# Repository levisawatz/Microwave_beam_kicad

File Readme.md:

# Steerable Microwave Beam Phased Array
Designer: Levi Sawatzky  
Overview Document: https://levisawatz.github.io/assets/microwave_beam/Project_summary.pdf  
Status: In production

## Project Overview 
This project explores the design and construction of a steerable microwave phased array capable of delivering a tightly focused beam of microwave energy toward a target. The system serves as a science demonstration platform that reveals the power and elegance of microwave circuit design, phased arrays, and high-frequency PCB engineering. The core concept is to electronically steer a beam of RF energy without any moving mechanical parts, using phase control across an array of patch antennas. This beam can then be used to transfer wireless power across a distance, light up LEDs, heat up food like a microwave, or boost WIFI 

This PCB was created using Kicad 10

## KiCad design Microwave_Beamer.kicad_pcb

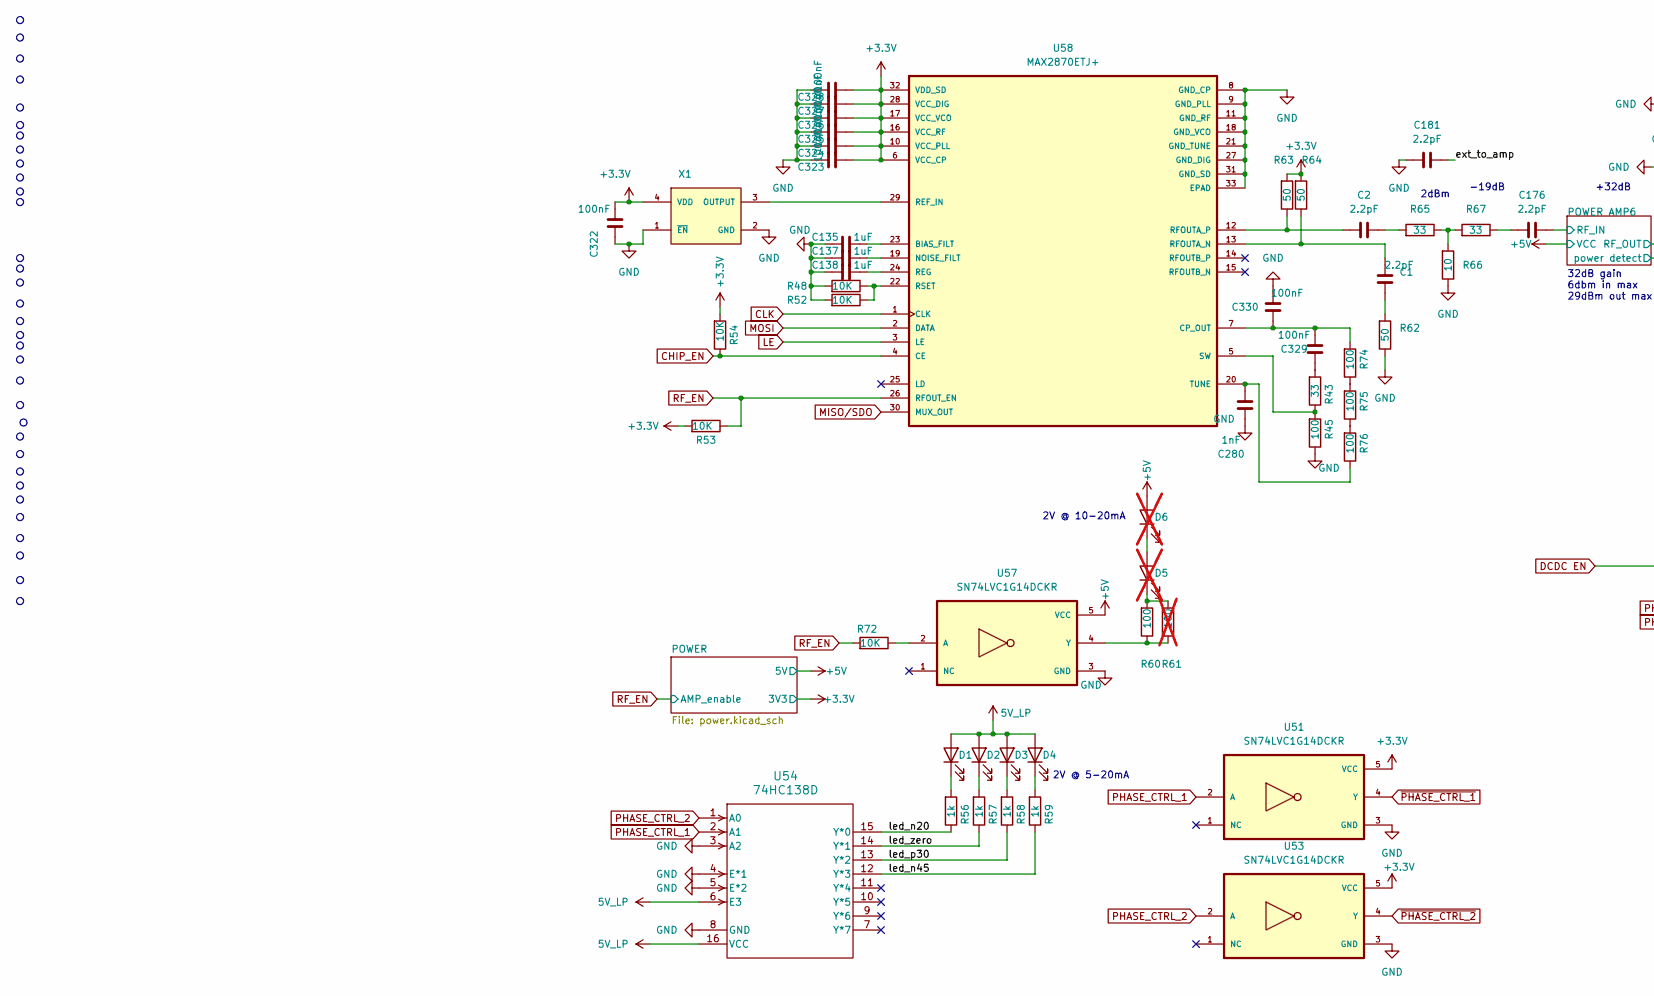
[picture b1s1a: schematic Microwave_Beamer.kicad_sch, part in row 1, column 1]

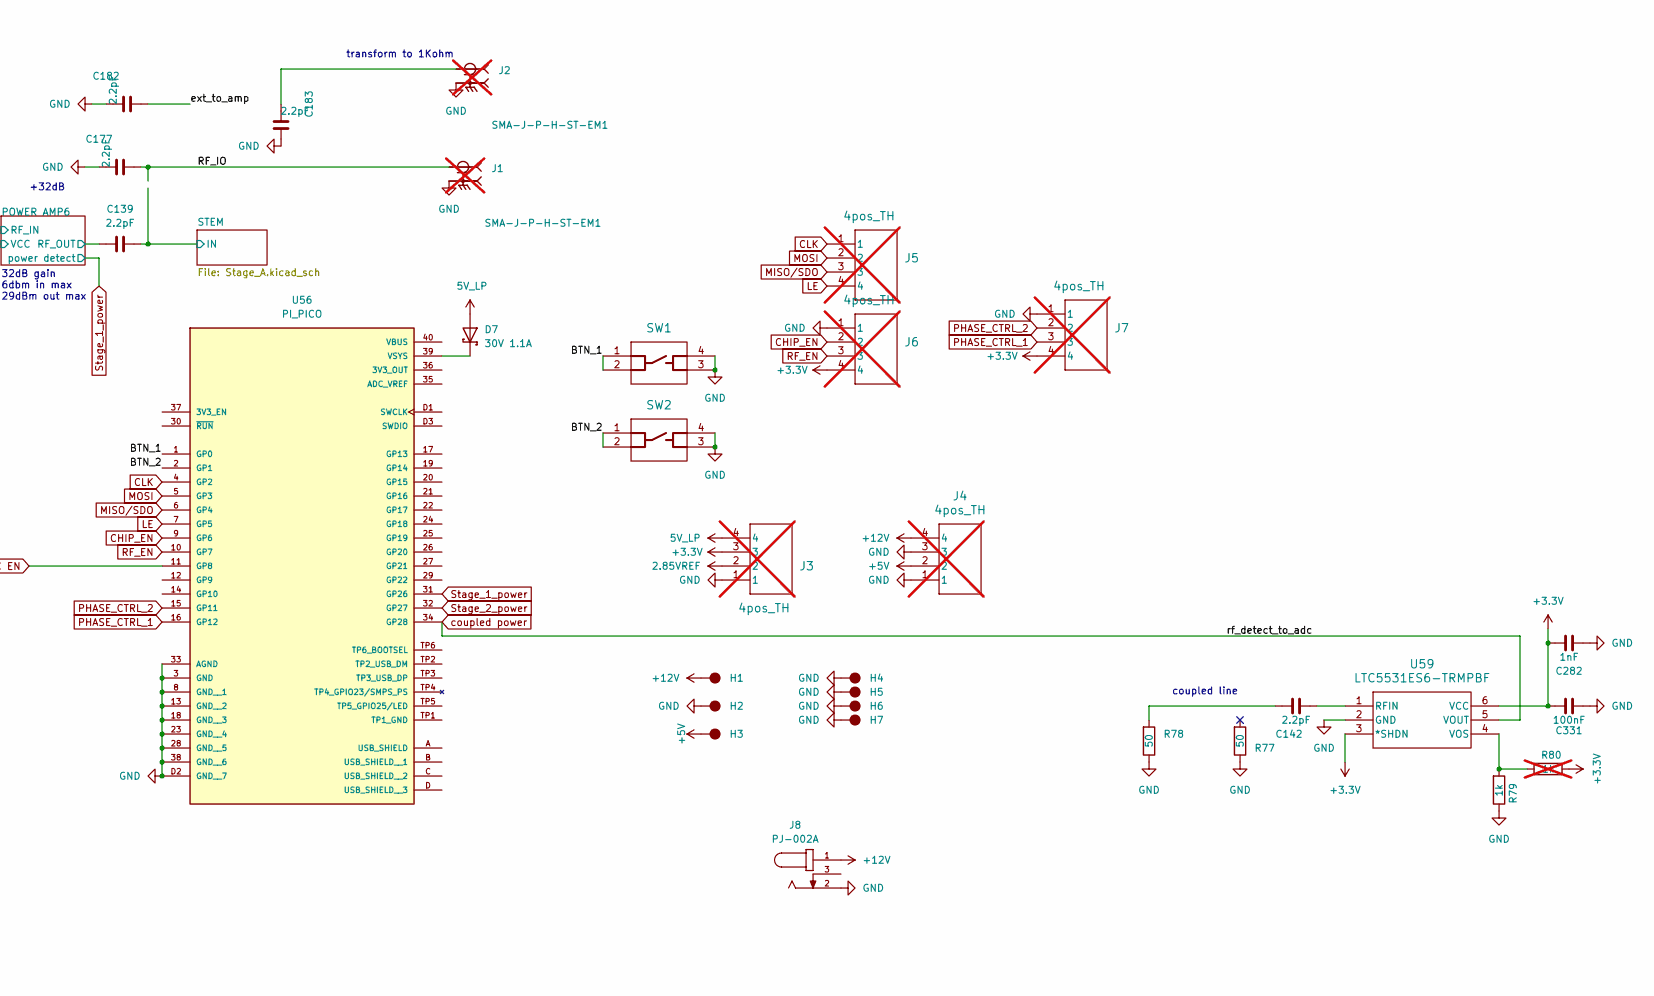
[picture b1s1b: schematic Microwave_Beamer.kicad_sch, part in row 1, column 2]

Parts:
C1, C2, C176: 2.2pF; C_0402_1005Metric; MPN GJM1555C1H2R2WB01D
C135, C137, C138: 1uF; C_0603_1608Metric; MPN GRT188R61H105KE13D
C139, C142, C177, C181, C182, C183: 2.2pF; C_0402_1005Metric_Pad0.74x0.62mm_HandSolder; MPN GJM1555C1H2R2WB01D
C280, C282: 1nF; C_0402_1005Metric; MPN GCM1555C1H102GA16J
C322, C323, C324, C325, C326, C327, C328, C329, C330, C331: 100nF; C_0402_1005Metric; MPN GCM155R71H104KE02J
D1, D2, D3, D4: LTST-C230KGKT; LED_1206_3216Metric; MPN LTST-C230KGKT
D5, D6: LTST-C230KGKT; LED_1206_3216Metric; MPN LTST-C230KRKT; not fitted
D7: 30V 1.1A; CR_03-GS08_VIS; MPN SL03-GS08
H1, H2, H3, H4, H5, H6, H7: Hole; PTH_5mm; MPN DNP
J1, J2: SMA-J-P-H-ST-EM1; SAMTEC_SMA-J-P-H-ST-EM1; PARTREV G; not fitted
J3, J4, J5, J6, J7: 4pos_TH; 4POS-2_54-generic; MPN DNP; not fitted
J8: PJ-002A; CUI_PJ-002A; MPN PJ-002A
R43, R65, R67: 33; R_0402_1005Metric; MPN TNPW040233R0DEED
R45, R60, R74, R75, R76: 100; R_0402_1005Metric; MPN ERA-2AED101X
R48, R52, R53, R54, R72: 10K; R_0603_1608Metric; MPN ERA-3AEB103V
R56, R57, R58, R59, R79: 1k; R_0603_1608Metric; MPN ERA-3AEB102V
R61: 100; R_0402_1005Metric; MPN ERA-2AED101X; not fitted
R62, R63, R64: 50; R_0402_1005Metric; MPN TNPW040249R9BEED
R66: 10; R_0402_1005Metric; MPN TNPW040210R0DEED
R77, R78: 50; R_0402_1005Metric_Pad0.72x0.64mm_HandSolder; MPN TNPW040249R9BEED
R80: 1k; R_0603_1608Metric; MPN ERA-3AEB102V; not fitted
SW1, SW2: PTS526SM15SMTR2 LFS; SON4_PTS526 SM15 SMTR2 LFS_CNK-M; MPN PTS526SM15SMTR2 LFS
U51, U53, U57: SN74LVC1G14DCKR; SOT65P210X110-5N; MPN SN74LVC1G14DCKR
U54: 74HC138D; SOT109-1_NXP; MPN MC74HC138ADR2G
U56: PI_PICO; PI_PICO_SMD; MPN SC0917
U58: MAX2870ETJ+; vco_QFN50P500X500X80-33N; MPN MAX2870ETJ+
U59: LTC5531ES6-TRMPBF; SOT-6_S_LIT-M; MPN LTC5531ES6#TRMPBF
X1: ECS-3225MVQ-1000-CN-TR; OSC_ECS-3225MVQ-1000-CN-TR; MPN ECS-3225MVQ-1000-CN-TR

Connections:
2.85VREF: J3.2; also elsewhere on the board
5V_LP: D1.2 (A), D2.2 (A), D3.2 (A), D4.2 (A), D7.A, J3.4, U54.6 (E3), U54.16 (VCC); also elsewhere on the board
+3.3V: C282.1, C322.2, C323.2, C324.2, C325.2, C326.2, C327.2, C328.2, C331.1, J3.3, J6.4, J7.4, R53.1, R54.1, R63.1, R64.1, R80.2, U51.5 (VCC), U53.5 (VCC), U58.6 (VCC_CP), U58.10 (VCC_PLL), U58.16 (VCC_RF), U58.17 (VCC_VCO), U58.28 (VCC_DIG), U58.32 (VDD_SD), U59.3 (*SHDN), U59.6 (VCC), X1.4 (VDD); also elsewhere on the board
+5V: D6.2 (A), H3.1, J4.2, U57.5 (VCC); also elsewhere on the board
+12V: H1.1, J4.4, J8.1; also elsewhere on the board
/BTN_1: SW1.1, SW1.2, U56.1 (GP0)
/BTN_2: SW2.1, SW2.2, U56.2 (GP1)
/POWER AMP6/RF_IN: C176.2; also elsewhere on the board
/POWER AMP6/RF_OUT: C139.1; also elsewhere on the board
/RF_IO: C177.2, J1.1
/STEM/IN: C139.2; also elsewhere on the board
/ext_to_amp: C181.2, C182.2
/led_n20: R56.2, U54.15 (Y*0)
/led_n45: R59.2, U54.12 (Y*3)
/led_p30: R58.2, U54.13 (Y*2)
/led_zero: R57.2, U54.14 (Y*1)
CHIP_EN: J6.2, R54.2, U56.9 (GP6), U58.4 (CE)
CLK: J5.1, U56.4 (GP2), U58.1 (CLK)
DCDC EN: U56.11 (GP8); also elsewhere on the board
GND: C135.1, C137.1, C138.1, C177.1, C181.1, C182.1, C183.2, C280.2, C282.2, C322.1, C323.1, C324.1, C325.1, C326.1, C327.1, C328.1, C330.1, C331.2, H2.1, H4.1, H5.1, H6.1, H7.1, J1.2_1, J1.2_2, J1.3_1, J1.3_2, J2.2_1, J2.2_2, J2.3_1, J2.3_2, J3.1, J4.1, J4.3, J6.1, J7.1, J8.2, R45.2, R48.1, R52.1, R62.2, R66.2, R77.2, R78.2, R79.2, SW1.3, SW1.4, SW2.3, SW2.4, U51.3 (GND), U53.3 (GND), U54.3 (A2), U54.4 (E*1), U54.5 (E*2), U54.8 (GND), U56.3 (GND), U56.8 (GND__1), U56.13 (GND__2), U56.18 (GND__3), U56.23 (GND__4), U56.28 (GND__5), U56.33 (AGND), U56.38 (GND__6), U56.D2 (GND__7), U57.3 (GND), U58.8 (GND_CP), U58.9 (GND_PLL), U58.11 (GND_RF), U58.18 (GND_VCO), U58.21 (GND_TUNE), U58.27 (GND_DIG), U58.31 (GND_SD), U58.33 (EPAD), U59.2 (GND), X1.1 (~EN), X1.2 (GND); also elsewhere on the board
LE: J5.4, U56.7 (GP5), U58.3 (LE)
MISO/SDO: J5.3, U56.6 (GP4), U58.30 (MUX_OUT)
MOSI: J5.2, U56.5 (GP3), U58.2 (DATA)
unnamed: C1.2, R62.1
unnamed: C2.2, R65.1
unnamed: C142.1, R78.1
unnamed: C176.1, R67.2
unnamed: C183.1, J2.1
unnamed: C329.2, R43.1
unnamed: D1.1 (K), R56.1
unnamed: D2.1 (K), R57.1
unnamed: D3.1 (K), R58.1
unnamed: D4.1 (K), R59.1
unnamed: D5.2 (A), D6.1 (K)
unnamed: D5.1 (K), R60.1, R61.1
unnamed: R65.2, R66.1, R67.1
unnamed: R74.2, R75.1
unnamed: R75.2, R76.1
unnamed: D7.K, U56.39 (VSYS)
unnamed: R72.2, U57.2 (A)
unnamed: R60.2, R61.2, U57.4 (Y)
unnamed: C135.2, U58.23 (BIAS_FILT)
unnamed: C329.1, C330.2, R74.1, U58.7 (CP_OUT)
unnamed: C137.2, U58.19 (NOISE_FILT)
unnamed: U58.29 (REF_IN), X1.3 (OUTPUT)
unnamed: C138.2, U58.24 (REG)
unnamed: C1.1, R64.2, U58.13 (RFOUTA_N)
unnamed: C2.1, R63.2, U58.12 (RFOUTA_P)
unnamed: R48.2, R52.2, U58.22 (RSET)
unnamed: R43.2, R45.1, U58.5 (SW)
unnamed: C280.1, R76.2, U58.20 (TUNE)
unnamed: C142.2, U59.1 (RFIN)
unnamed: R79.1, R80.1, U59.4 (VOS)
PHASE_CTRL_1: J7.3, U51.2 (A), U54.2 (A1), U56.16 (GP12); also elsewhere on the board
PHASE_CTRL_2: J7.2, U53.2 (A), U54.1 (A0), U56.15 (GP11); also elsewhere on the board
RF_EN: J6.3, R53.2, R72.1, U56.10 (GP7), U58.26 (RFOUT_EN); also elsewhere on the board
Stage_1_power: U56.31 (GP26); also elsewhere on the board
Stage_2_power: U56.32 (GP27); also elsewhere on the board
coupled power: U56.34 (GP28), U59.5 (VOUT)
~PHASE_CTRL_1: U51.4 (Y); also elsewhere on the board
~PHASE_CTRL_2: U53.4 (Y); also elsewhere on the board

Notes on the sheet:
coupled line
2V @ 10-20mA
32dB gain 6dbm in max 29dBm out max
2dBm
-19dB
transform to 1Kohm
2V @ 5-20mA
+32dB

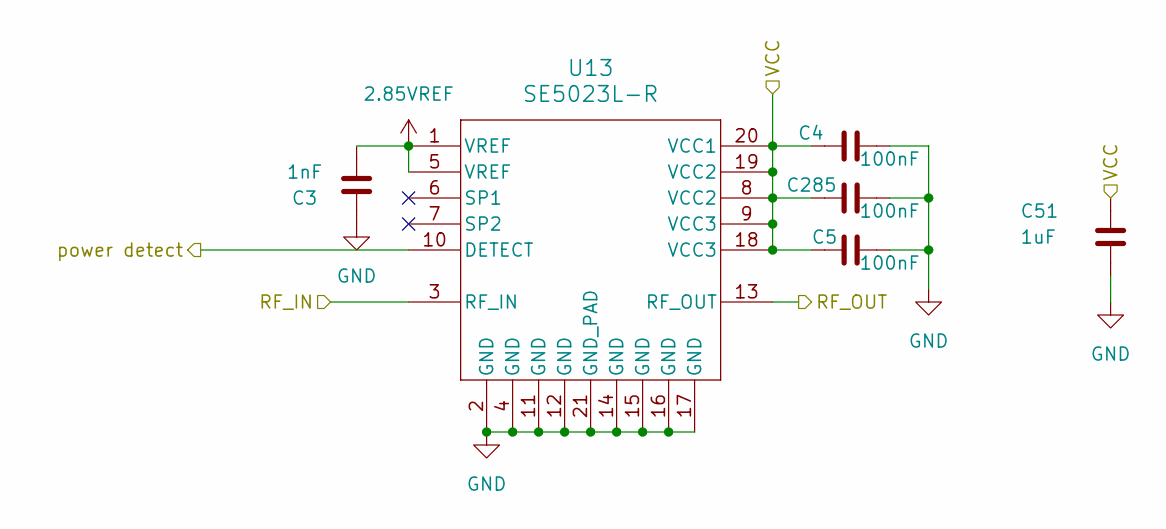
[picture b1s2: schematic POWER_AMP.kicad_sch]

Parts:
C3: 1nF; C_0402_1005Metric; MPN GCM1555C1H102GA16J
C4, C5, C285: 100nF; C_0402_1005Metric; MPN GCM155R71H104KE02J
C51: 1uF; C_0603_1608Metric; MPN GRT188R61H105KE13D
U13: SE5023L-R; QFN20_4X4_STM; MPN SE5023L-R

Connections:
2.85VREF: C3.1, U13.1 (VREF), U13.5 (VREF); also elsewhere on the board
+5V: C4.1, C5.1, C51.1, C285.1, U13.8 (VCC2), U13.9 (VCC3), U13.18 (VCC3), U13.19 (VCC2), U13.20 (VCC1); also elsewhere on the board
/STEM/FAN_A/Antenna_1: U13.13 (RF_OUT)
/STEM/FAN_A/FANFAN A/OUT1: U13.3 (RF_IN); also elsewhere on the board
/STEM/FAN_A/POWER AMP1/power detect: U13.10 (DETECT)
GND: C3.2, C4.2, C5.2, C51.2, C285.2, U13.2 (GND), U13.4 (GND), U13.11 (GND), U13.12 (GND), U13.14 (GND), U13.15 (GND), U13.16 (GND), U13.17 (GND), U13.21 (GND_PAD); also elsewhere on the board

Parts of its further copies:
C6, C7, C8, C9, C25, C26, C27, C28, C29, C30, C39, C40, C41, C42, C43, C44, C46, C47, C48, C49, C50, C61, C75, C89, C103, C117, C131, C145, C159, C173, C187, C201, C215, C229, C243, C257, C286, C287, C288, C289, C290, C291, C292, C293, C294, C295, C296, C297, C298, C299, C300, C301, C302, C303: 100nF; C_0402_1005Metric; MPN GCM155R71H104KE02J
C24, C38, C45, C59, C73, C87, C101, C115, C129, C143, C157, C171, C185, C199, C213, C227, C241, C255: 1nF; C_0402_1005Metric; MPN GCM1555C1H102GA16J
C60, C62, C63, C64, C65, C74, C76, C77, C78, C79, C88, C90, C91, C92, C93, C102, C104, C105: 1uF; C_0603_1608Metric; MPN GRT188R61H105KE13D
U16, U18, U19, U21, U23, U25, U27, U29, U31, U33, U35, U37, U39, U41, U43, U45, U47, U49: SE5023L-R; QFN20_4X4_STM; MPN SE5023L-R

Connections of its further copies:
2.85VREF: C24.1, C38.1, C45.1, C59.1, C73.1, C87.1, C101.1, C115.1, C129.1, C143.1, C157.1, C171.1, C185.1, C199.1, C213.1, C227.1, C241.1, C255.1, U16.1 (VREF), U16.5 (VREF), U18.1 (VREF), U18.5 (VREF), U19.1 (VREF), U19.5 (VREF), U21.1 (VREF), U21.5 (VREF), U23.1 (VREF), U23.5 (VREF), U25.1 (VREF), U25.5 (VREF), U27.1 (VREF), U27.5 (VREF), U29.1 (VREF), U29.5 (VREF), U31.1 (VREF), U31.5 (VREF), U33.1 (VREF), U33.5 (VREF), U35.1 (VREF), U35.5 (VREF), U37.1 (VREF), U37.5 (VREF), U39.1 (VREF), U39.5 (VREF), U41.1 (VREF), U41.5 (VREF), U43.1 (VREF), U43.5 (VREF), U45.1 (VREF), U45.5 (VREF), U47.1 (VREF), U47.5 (VREF), U49.1 (VREF), U49.5 (VREF); also elsewhere on the board
+5V: C6.1, C7.1, C8.1, C9.1, C25.1, C26.1, C27.1, C28.1, C29.1, C30.1, C39.1, C40.1, C41.1, C42.1, C43.1, C44.1, C46.1, C47.1, C48.1, C49.1, C50.1, C60.1, C61.1, C62.1, C63.1, C64.1, C65.1, C74.1, C75.1, C76.1, C77.1, C78.1, C79.1, C88.1, C89.1, C90.1, C91.1, C92.1, C93.1, C102.1, C103.1, C104.1, C105.1, C117.1, C131.1, C145.1, C159.1, C173.1, C187.1, C201.1, C215.1, C229.1, C243.1, C257.1, C286.1, C287.1, C288.1, C289.1, C290.1, C291.1, C292.1, C293.1, C294.1, C295.1, C296.1, C297.1, C298.1, C299.1, C300.1, C301.1, C302.1, C303.1, U16.8 (VCC2), U16.9 (VCC3), U16.18 (VCC3), U16.19 (VCC2), U16.20 (VCC1), U18.8 (VCC2), U18.9 (VCC3), U18.18 (VCC3), U18.19 (VCC2), U18.20 (VCC1), U19.8 (VCC2), U19.9 (VCC3), U19.18 (VCC3), U19.19 (VCC2), U19.20 (VCC1), U21.8 (VCC2), U21.9 (VCC3), U21.18 (VCC3), U21.19 (VCC2), U21.20 (VCC1), U23.8 (VCC2), U23.9 (VCC3), U23.18 (VCC3), U23.19 (VCC2), U23.20 (VCC1), U25.8 (VCC2), U25.9 (VCC3), U25.18 (VCC3), U25.19 (VCC2), U25.20 (VCC1), U27.8 (VCC2), U27.9 (VCC3), U27.18 (VCC3), U27.19 (VCC2), U27.20 (VCC1), U29.8 (VCC2), U29.9 (VCC3), U29.18 (VCC3), U29.19 (VCC2), U29.20 (VCC1), U31.8 (VCC2), U31.9 (VCC3), U31.18 (VCC3), U31.19 (VCC2), U31.20 (VCC1), U33.8 (VCC2), U33.9 (VCC3), U33.18 (VCC3), U33.19 (VCC2), U33.20 (VCC1), U35.8 (VCC2), U35.9 (VCC3), U35.18 (VCC3), U35.19 (VCC2), U35.20 (VCC1), U37.8 (VCC2), U37.9 (VCC3), U37.18 (VCC3), U37.19 (VCC2), U37.20 (VCC1), U39.8 (VCC2), U39.9 (VCC3), U39.18 (VCC3), U39.19 (VCC2), U39.20 (VCC1), U41.8 (VCC2), U41.9 (VCC3), U41.18 (VCC3), U41.19 (VCC2), U41.20 (VCC1), U43.8 (VCC2), U43.9 (VCC3), U43.18 (VCC3), U43.19 (VCC2), U43.20 (VCC1), U45.8 (VCC2), U45.9 (VCC3), U45.18 (VCC3), U45.19 (VCC2), U45.20 (VCC1), U47.8 (VCC2), U47.9 (VCC3), U47.18 (VCC3), U47.19 (VCC2), U47.20 (VCC1), U49.8 (VCC2), U49.9 (VCC3), U49.18 (VCC3), U49.19 (VCC2), U49.20 (VCC1); also elsewhere on the board
/POWER AMP6/RF_IN: U49.3 (RF_IN); also elsewhere on the board
/POWER AMP6/RF_OUT: U49.13 (RF_OUT); also elsewhere on the board
/STEM/FAN_A/Antenna_3: U16.13 (RF_OUT)
/STEM/FAN_A/Antenna_5: U18.13 (RF_OUT)
/STEM/FAN_A/FANFAN A/OUT3: U16.3 (RF_IN); also elsewhere on the board
/STEM/FAN_A/FANFAN A/OUT5: U18.3 (RF_IN); also elsewhere on the board
/STEM/FAN_A/POWER AMP3/power detect: U16.10 (DETECT)
/STEM/FAN_A/power_det: U18.10 (DETECT)
/STEM/FAN_B/Antenna_1: U19.13 (RF_OUT)
/STEM/FAN_B/Antenna_3: U21.13 (RF_OUT)
/STEM/FAN_B/Antenna_5: U23.13 (RF_OUT)
/STEM/FAN_B/FANFAN A/OUT1: U19.3 (RF_IN); also elsewhere on the board
/STEM/FAN_B/FANFAN A/OUT3: U21.3 (RF_IN); also elsewhere on the board
/STEM/FAN_B/FANFAN A/OUT5: U23.3 (RF_IN); also elsewhere on the board
/STEM/FAN_B/POWER AMP1/power detect: U19.10 (DETECT)
/STEM/FAN_B/POWER AMP3/power detect: U21.10 (DETECT)
/STEM/FAN_C/Antenna_1: U25.13 (RF_OUT)
/STEM/FAN_C/Antenna_3: U27.13 (RF_OUT)
/STEM/FAN_C/Antenna_5: U29.13 (RF_OUT)
/STEM/FAN_C/FANFAN A/OUT1: U25.3 (RF_IN); also elsewhere on the board
/STEM/FAN_C/FANFAN A/OUT3: U27.3 (RF_IN); also elsewhere on the board
/STEM/FAN_C/FANFAN A/OUT5: U29.3 (RF_IN); also elsewhere on the board
/STEM/FAN_C/POWER AMP1/power detect: U25.10 (DETECT)
/STEM/FAN_C/POWER AMP3/power detect: U27.10 (DETECT)
/STEM/FAN_C/power_det: U29.10 (DETECT)
/STEM/FAN_D/Antenna_1: U31.13 (RF_OUT)
/STEM/FAN_D/Antenna_3: U33.13 (RF_OUT)
/STEM/FAN_D/Antenna_5: U35.13 (RF_OUT)
/STEM/FAN_D/FANFAN A/OUT1: U31.3 (RF_IN); also elsewhere on the board
/STEM/FAN_D/FANFAN A/OUT3: U33.3 (RF_IN); also elsewhere on the board
/STEM/FAN_D/FANFAN A/OUT5: U35.3 (RF_IN); also elsewhere on the board
/STEM/FAN_D/POWER AMP1/power detect: U31.10 (DETECT)
/STEM/FAN_D/POWER AMP3/power detect: U33.10 (DETECT)
/STEM/FAN_D/power_det: U35.10 (DETECT)
/STEM/FAN_E/Antenna_1: U37.13 (RF_OUT)
/STEM/FAN_E/Antenna_3: U39.13 (RF_OUT)
/STEM/FAN_E/Antenna_5: U41.13 (RF_OUT)
/STEM/FAN_E/FANFAN A/OUT1: U37.3 (RF_IN); also elsewhere on the board
/STEM/FAN_E/FANFAN A/OUT3: U39.3 (RF_IN); also elsewhere on the board
/STEM/FAN_E/FANFAN A/OUT5: U41.3 (RF_IN); also elsewhere on the board
/STEM/FAN_E/POWER AMP1/power detect: U37.10 (DETECT)
/STEM/FAN_E/POWER AMP3/power detect: U39.10 (DETECT)
/STEM/FAN_E/power_det: U41.10 (DETECT)
/STEM/FAN_F/Antenna_1: U43.13 (RF_OUT)
/STEM/FAN_F/Antenna_3: U45.13 (RF_OUT)
/STEM/FAN_F/Antenna_5: U47.13 (RF_OUT)
/STEM/FAN_F/FANFAN A/OUT1: U43.3 (RF_IN); also elsewhere on the board
/STEM/FAN_F/FANFAN A/OUT3: U45.3 (RF_IN); also elsewhere on the board
/STEM/FAN_F/FANFAN A/OUT5: U47.3 (RF_IN); also elsewhere on the board
/STEM/FAN_F/POWER AMP1/power detect: U43.10 (DETECT)
/STEM/FAN_F/POWER AMP3/power detect: U45.10 (DETECT)
/STEM/FAN_F/power_det: U47.10 (DETECT)
GND: C6.2, C7.2, C8.2, C9.2, C24.2, C25.2, C26.2, C27.2, C28.2, C29.2, C30.2, C38.2, C39.2, C40.2, C41.2, C42.2, C43.2, C44.2, C45.2, C46.2, C47.2, C48.2, C49.2, C50.2, C59.2, C60.2, C61.2, C62.2, C63.2, C64.2, C65.2, C73.2, C74.2, C75.2, C76.2, C77.2, C78.2, C79.2, C87.2, C88.2, C89.2, C90.2, C91.2, C92.2, C93.2, C101.2, C102.2, C103.2, C104.2, C105.2, C115.2, C117.2, C129.2, C131.2, C143.2, C145.2, C157.2, C159.2, C171.2, C173.2, C185.2, C187.2, C199.2, C201.2, C213.2, C215.2, C227.2, C229.2, C241.2, C243.2, C255.2, C257.2, C286.2, C287.2, C288.2, C289.2, C290.2, C291.2, C292.2, C293.2, C294.2, C295.2, C296.2, C297.2, C298.2, C299.2, C300.2, C301.2, C302.2, C303.2, U16.2 (GND), U16.4 (GND), U16.11 (GND), U16.12 (GND), U16.14 (GND), U16.15 (GND), U16.16 (GND), U16.17 (GND), U16.21 (GND_PAD), U18.2 (GND), U18.4 (GND), U18.11 (GND), U18.12 (GND), U18.14 (GND), U18.15 (GND), U18.16 (GND), U18.17 (GND), U18.21 (GND_PAD), U19.2 (GND), U19.4 (GND), U19.11 (GND), U19.12 (GND), U19.14 (GND), U19.15 (GND), U19.16 (GND), U19.17 (GND), U19.21 (GND_PAD), U21.2 (GND), U21.4 (GND), U21.11 (GND), U21.12 (GND), U21.14 (GND), U21.15 (GND), U21.16 (GND), U21.17 (GND), U21.21 (GND_PAD), U23.2 (GND), U23.4 (GND), U23.11 (GND), U23.12 (GND), U23.14 (GND), U23.15 (GND), U23.16 (GND), U23.17 (GND), U23.21 (GND_PAD), U25.2 (GND), U25.4 (GND), U25.11 (GND), U25.12 (GND), U25.14 (GND), U25.15 (GND), U25.16 (GND), U25.17 (GND), U25.21 (GND_PAD), U27.2 (GND), U27.4 (GND), U27.11 (GND), U27.12 (GND), U27.14 (GND), U27.15 (GND), U27.16 (GND), U27.17 (GND), U27.21 (GND_PAD), U29.2 (GND), U29.4 (GND), U29.11 (GND), U29.12 (GND), U29.14 (GND), U29.15 (GND), U29.16 (GND), U29.17 (GND), U29.21 (GND_PAD), U31.2 (GND), U31.4 (GND), U31.11 (GND), U31.12 (GND), U31.14 (GND), U31.15 (GND), U31.16 (GND), U31.17 (GND), U31.21 (GND_PAD), U33.2 (GND), U33.4 (GND), U33.11 (GND), U33.12 (GND), U33.14 (GND), U33.15 (GND), U33.16 (GND), U33.17 (GND), U33.21 (GND_PAD), U35.2 (GND), U35.4 (GND), U35.11 (GND), U35.12 (GND), U35.14 (GND), U35.15 (GND), U35.16 (GND), U35.17 (GND), U35.21 (GND_PAD), U37.2 (GND), U37.4 (GND), U37.11 (GND), U37.12 (GND), U37.14 (GND), U37.15 (GND), U37.16 (GND), U37.17 (GND), U37.21 (GND_PAD), U39.2 (GND), U39.4 (GND), U39.11 (GND), U39.12 (GND), U39.14 (GND), U39.15 (GND), U39.16 (GND), U39.17 (GND), U39.21 (GND_PAD), U41.2 (GND), U41.4 (GND), U41.11 (GND), U41.12 (GND), U41.14 (GND), U41.15 (GND), U41.16 (GND), U41.17 (GND), U41.21 (GND_PAD), U43.2 (GND), U43.4 (GND), U43.11 (GND), U43.12 (GND), U43.14 (GND), U43.15 (GND), U43.16 (GND), U43.17 (GND), U43.21 (GND_PAD), U45.2 (GND), U45.4 (GND), U45.11 (GND), U45.12 (GND), U45.14 (GND), U45.15 (GND), U45.16 (GND), U45.17 (GND), U45.21 (GND_PAD), U47.2 (GND), U47.4 (GND), U47.11 (GND), U47.12 (GND), U47.14 (GND), U47.15 (GND), U47.16 (GND), U47.17 (GND), U47.21 (GND_PAD), U49.2 (GND), U49.4 (GND), U49.11 (GND), U49.12 (GND), U49.14 (GND), U49.15 (GND), U49.16 (GND), U49.17 (GND), U49.21 (GND_PAD); also elsewhere on the board
Stage_1_power: U49.10 (DETECT); also elsewhere on the board
Stage_2_power: U23.10 (DETECT); also elsewhere on the board

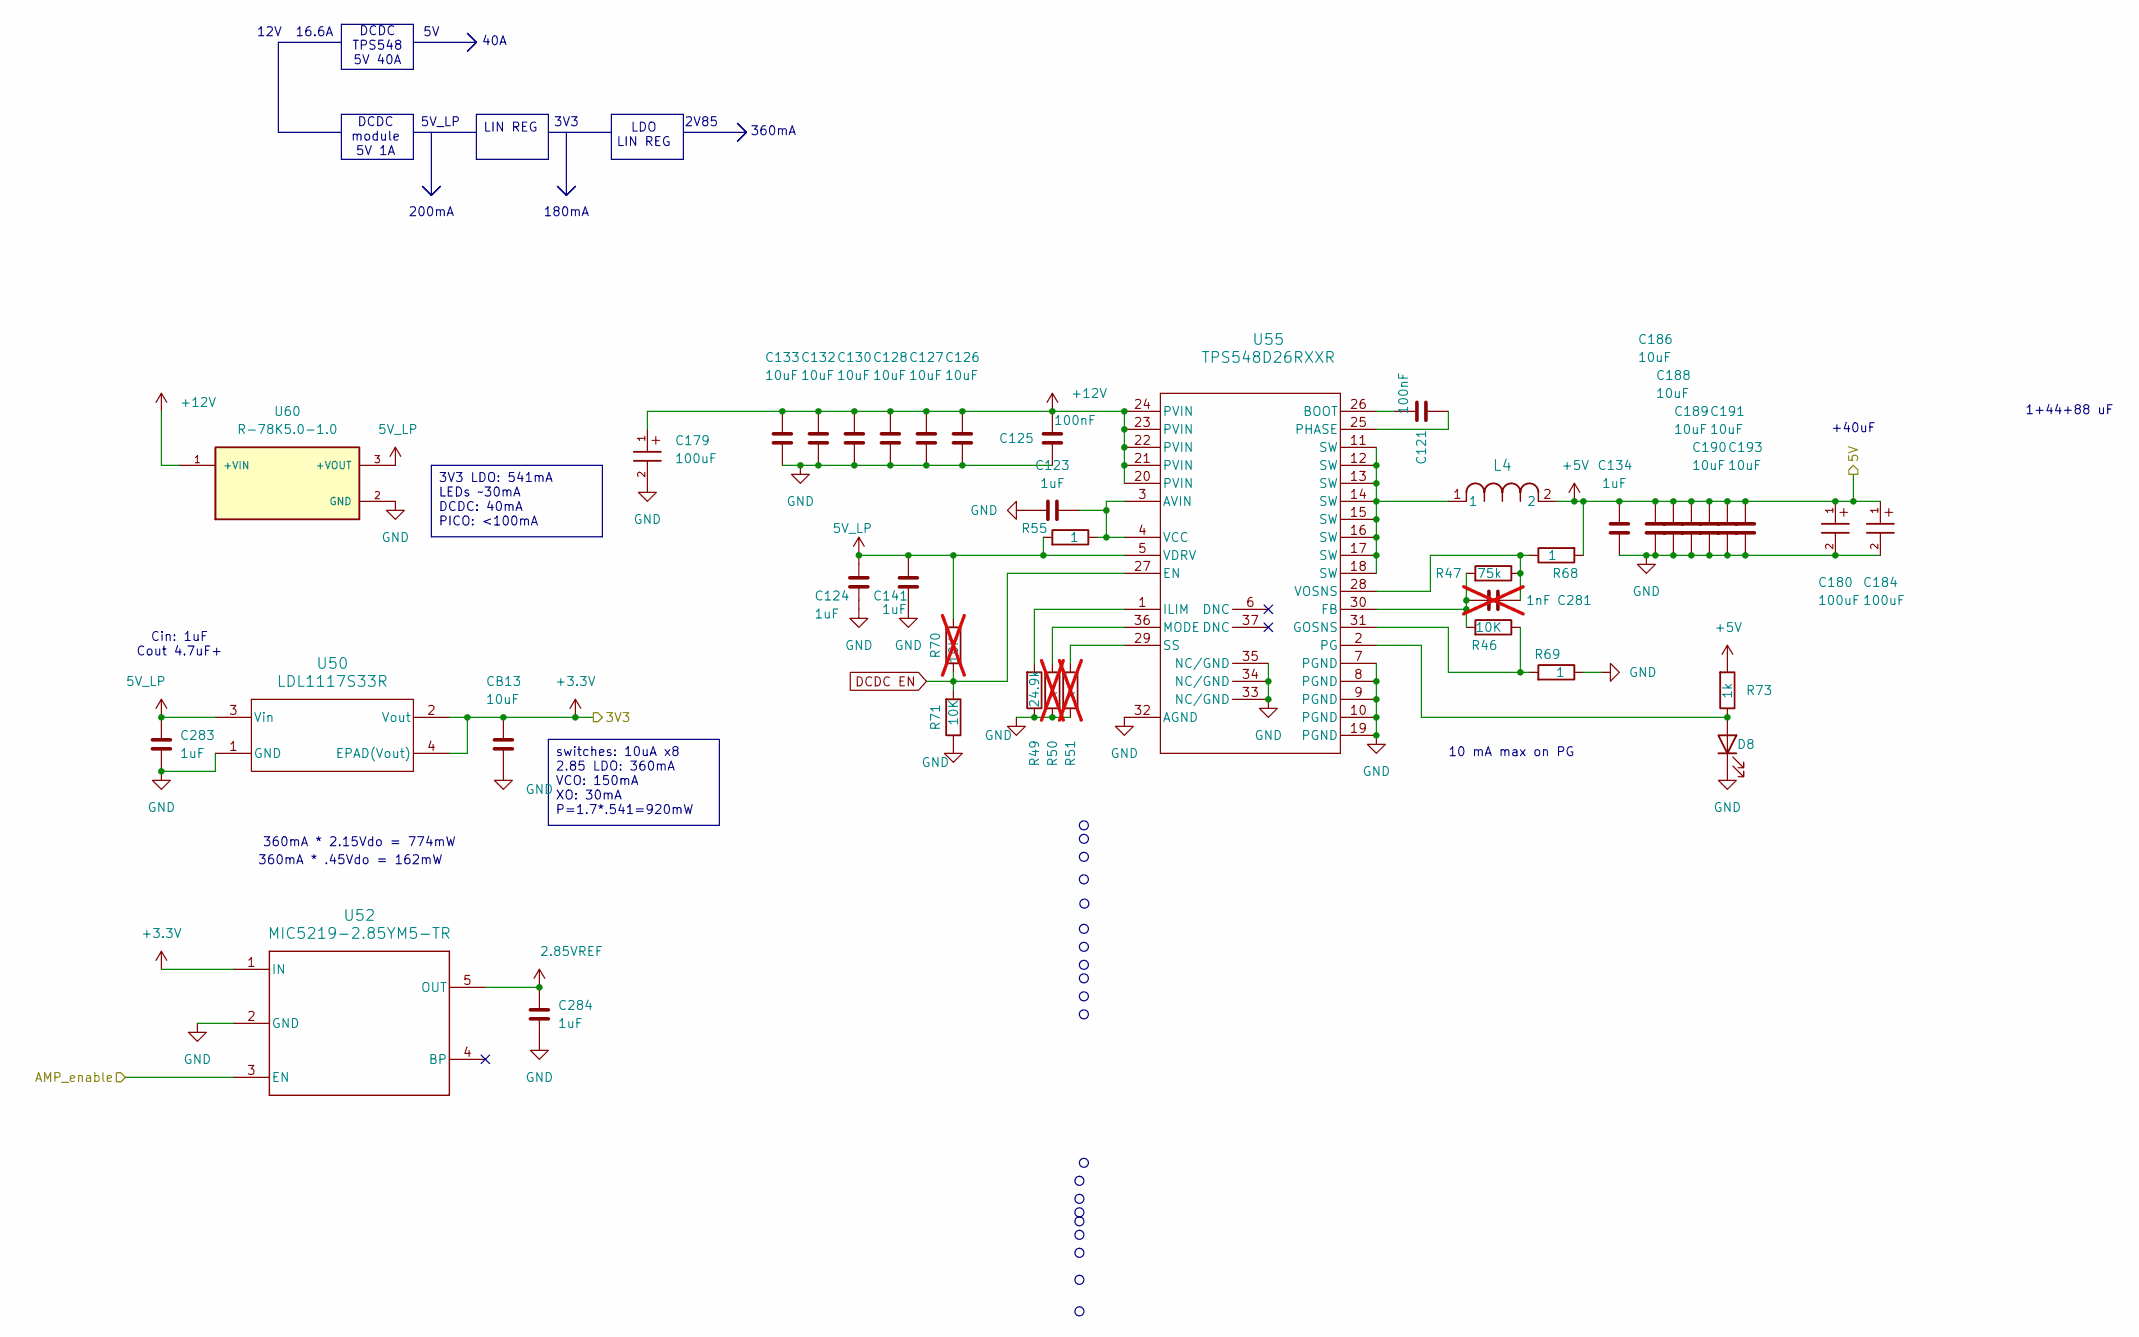
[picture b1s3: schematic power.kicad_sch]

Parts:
C121, C125: 100nF; C_0402_1005Metric; MPN GCM155R71H104KE02J
C123, C124, C134, C141, C283, C284: 1uF; C_0603_1608Metric; MPN GRT188R61H105KE13D
C126, C127, C128, C130, C132, C133, C186, C188, C189, C190, C191, C193: 10uF; C_1206_3216Metric; MPN GRT31CR61H106KE01L
C179, C180, C184: 100uF; WCAP-ASLI_6.3X7.7_DXL_; MPN 865080545012
C281: 1nF; C_0402_1005Metric; MPN GCM1555C1H102GA16J; not fitted
CB13: 10uF; C_1206_3216Metric; MPN GRT31CR61H106KE01L
D8: LTST-C230KGKT; LED_1206_3216Metric; MPN LTST-C230KGKT
L4: IHLP6767GZERR47M11; IND_IHLP-6767GZ_VIS; MPN IHLP6767GZERR47M11
R46, R71: 10K; R_0603_1608Metric; MPN ERA-3AEB103V
R47: 75k; R_0603_1608Metric; MPN ERA-3AEB753V
R49: 24.9k; R_0603_1608Metric; MPN ERA-3AEB2492V
R50, R51: x; R_0603_1608Metric; MPN x; not fitted
R55, R68, R69: 1; R_0603_1608Metric; MPN ERJ-3RQF1R0V
R70: 10K; R_0603_1608Metric; MPN ERA-3AEB103V; not fitted
R73: 1k; R_0603_1608Metric; MPN ERA-3AEB102V
U50: LDL1117S33R; SOT-223_DIO; MPN LDL1117S33R (LDI1117-3.3H)
U52: MIC5219-2.85YM5-TR; SOT23-5; MPN MIC5219-2.85YM5-TR
U55: TPS548D26RXXR; WQFN_C26RXXR_TEX; MPN TPS548D26RXXR
U60: R-78K5.0-1.0; DCDC_R-78K3.3-0.5; MPN R-78K5.0-1.0

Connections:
2.85VREF: C284.1, U52.5 (OUT); also elsewhere on the board
5V_LP: C124.1, C141.1, C283.1, R55.1, R70.2, U50.3 (Vin), U55.5 (VDRV), U60.3 (+VOUT); also elsewhere on the board
+3.3V: CB13.1, U50.2 (Vout), U50.4 (EPAD(Vout)), U52.1 (IN); also elsewhere on the board
+5V: C134.1, C180.1, C184.1, C186.1, C188.1, C189.1, C190.1, C191.1, C193.1, L4.2, R68.1, R73.1; also elsewhere on the board
+12V: C125.1, C126.1, C127.1, C128.1, C130.1, C132.1, C133.1, C179.1, U55.20 (PVIN), U55.21 (PVIN), U55.22 (PVIN), U55.23 (PVIN), U55.24 (PVIN), U60.1 (+VIN); also elsewhere on the board
DCDC EN: R70.1, R71.1, U55.27 (EN); also elsewhere on the board
GND: C123.2, C124.2, C125.2, C126.2, C127.2, C128.2, C130.2, C132.2, C133.2, C134.2, C141.2, C179.2, C180.2, C184.2, C186.2, C188.2, C189.2, C190.2, C191.2, C193.2, C283.2, C284.2, CB13.2, D8.1 (K), R49.2, R50.2, R51.2, R69.2, R71.2, U50.1 (GND), U52.2 (GND), U55.7 (PGND), U55.8 (PGND), U55.9 (PGND), U55.10 (PGND), U55.19 (PGND), U55.32 (AGND), U55.33 (NC/GND), U55.34 (NC/GND), U55.35 (NC/GND), U60.2 (GND); also elsewhere on the board
unnamed: D8.2 (A), R73.2, U55.2 (PG)
unnamed: L4.1, U55.11 (SW), U55.12 (SW), U55.13 (SW), U55.14 (SW), U55.15 (SW), U55.16 (SW), U55.17 (SW), U55.18 (SW)
unnamed: C123.1, R55.2, U55.3 (AVIN), U55.4 (VCC)
unnamed: C121.1, U55.26 (BOOT)
unnamed: C281.1, R46.1, R47.1, U55.30 (FB)
unnamed: R46.2, R69.1, U55.31 (GOSNS)
unnamed: R49.1, U55.1 (ILIM)
unnamed: R50.1, U55.36 (MODE)
unnamed: C121.2, U55.25 (PHASE)
unnamed: R51.1, U55.29 (SS)
unnamed: C281.2, R47.2, R68.2, U55.28 (VOSNS)
RF_EN: U52.3 (EN); also elsewhere on the board

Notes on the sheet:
360mA * .45Vdo = 162mW
2V85
LIN REG
180mA
360mA * 2.15Vdo = 774mW
5V_LP
16.6A
1+44+88 uF
360mA
200mA
DCDC module 5V 1A
Cin: 1uF Cout 4.7uF+
3V3
LDO LIN REG
10 mA max on PG
+40uF
40A
DCDC TPS548 5V 40A
12V
switches: 10uA x8 2.85 LDO: 360mA VCO: 150mA XO: 30mA P=1.7*.541=920mW
3V3 LDO: 541mA LEDs ~30mA DCDC: 40mA PICO: <100mA

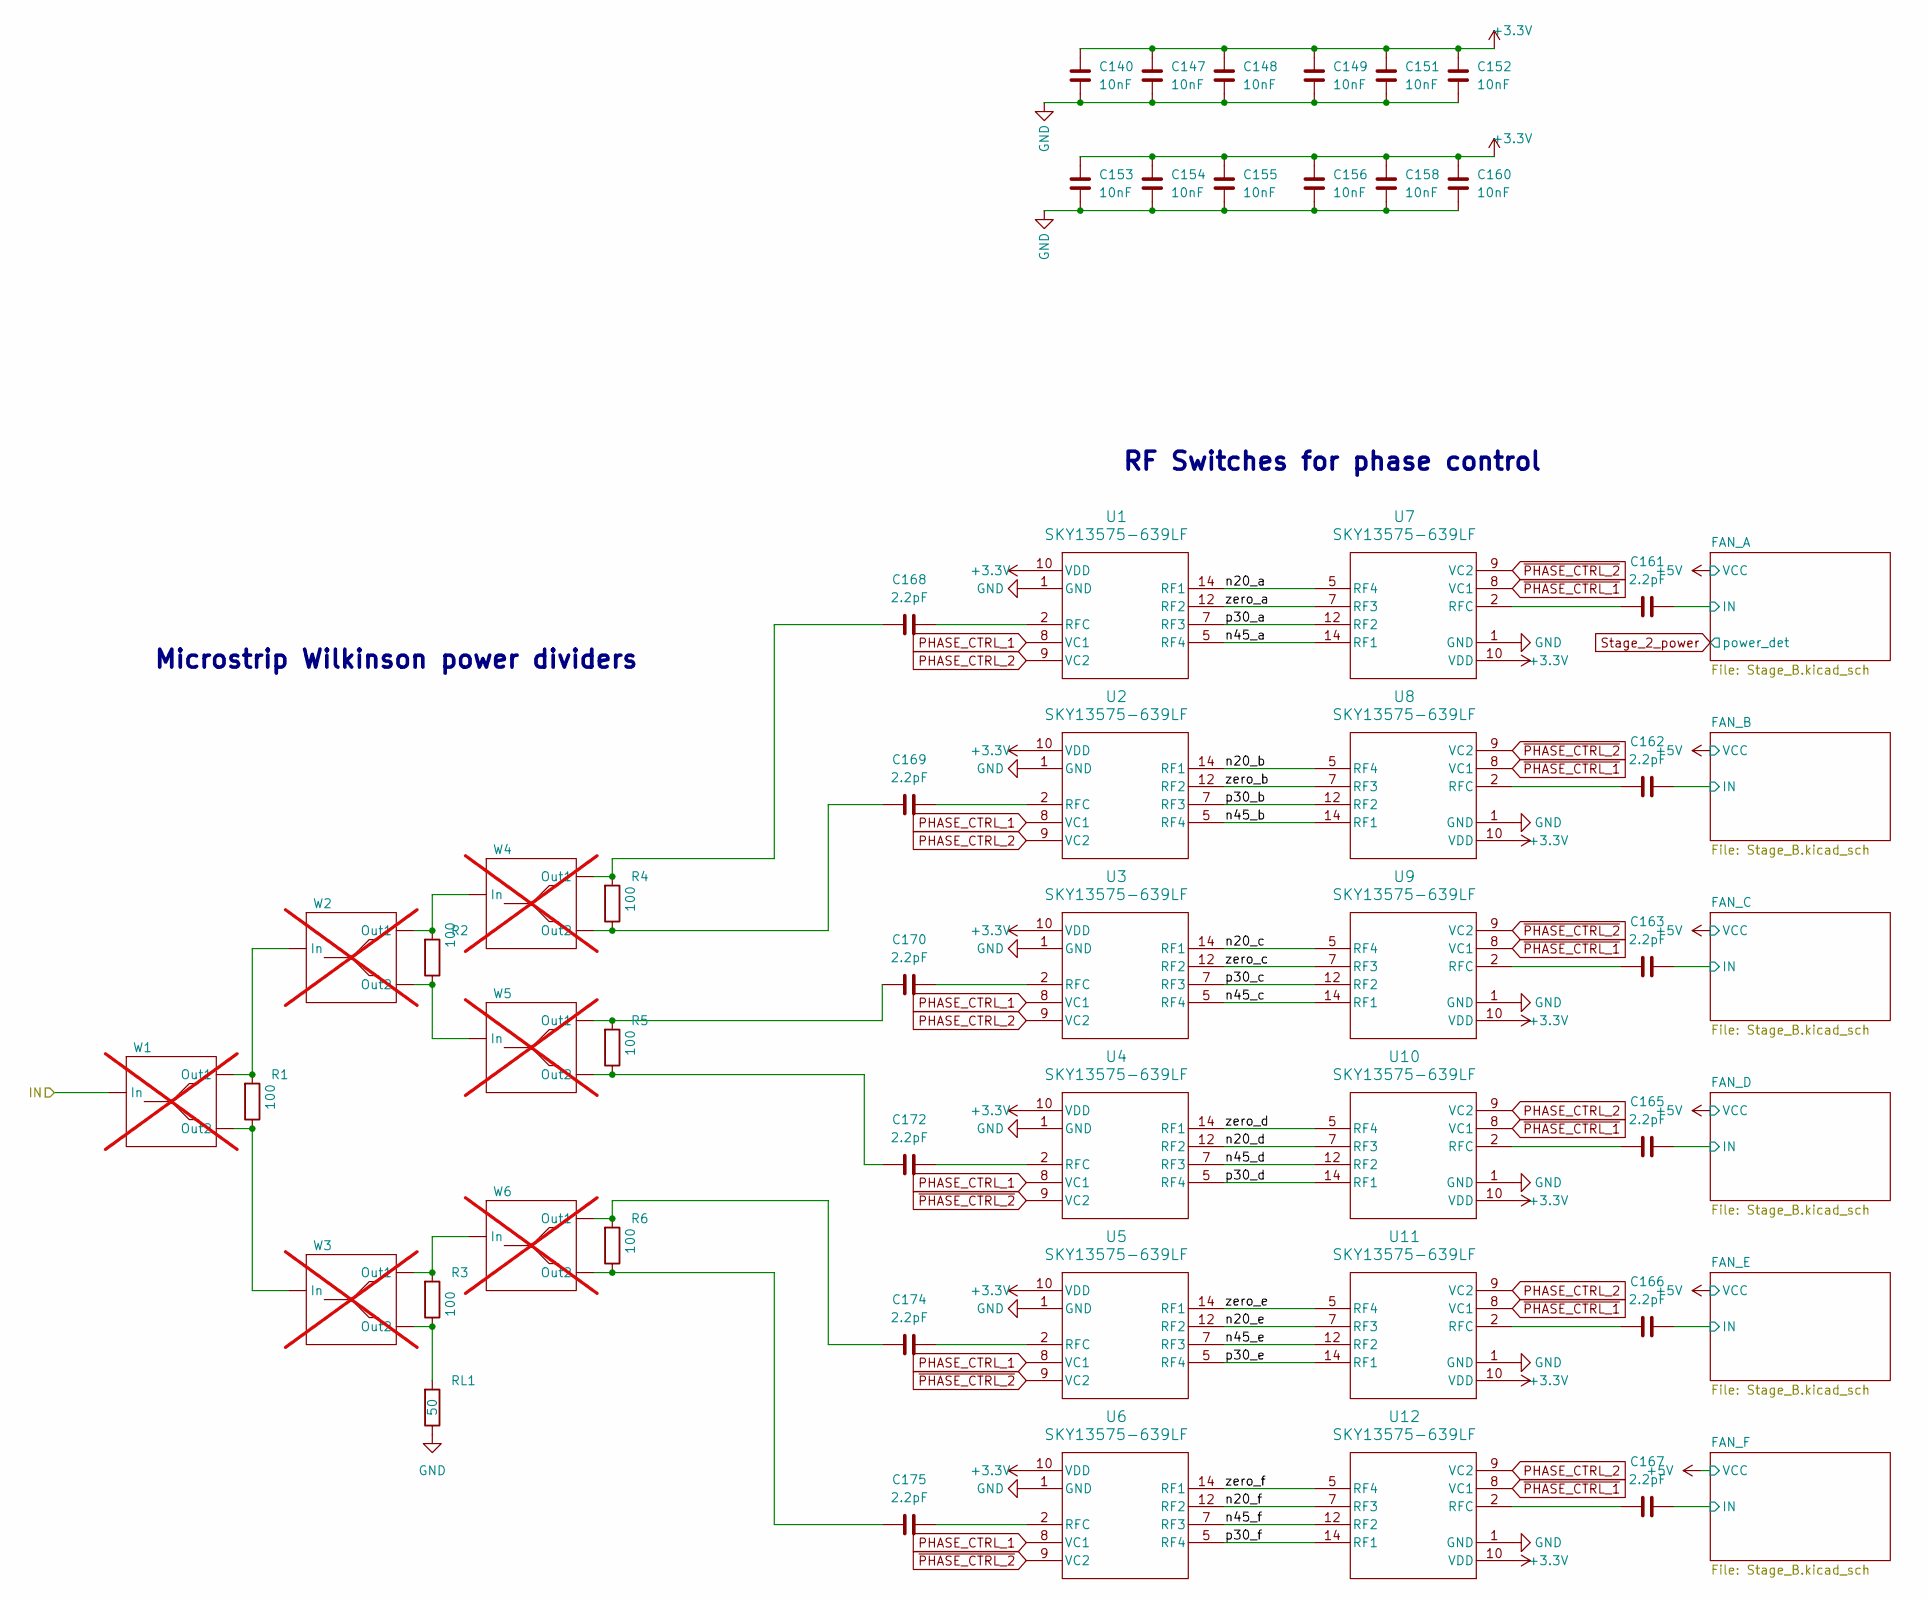
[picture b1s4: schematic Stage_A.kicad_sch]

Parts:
C140, C147, C148, C149, C151, C152, C153, C154, C155, C156, C158, C160: 10nF; C_0402_1005Metric; MPN GCM155R71H103KA55D
C161, C162, C163, C165, C166, C167, C168, C169, C170, C172, C174, C175: 2.2pF; C_0402_1005Metric; MPN GJM1555C1H2R2WB01D
R1, R2, R3, R4, R5, R6: 100; R_0402_1005Metric; MPN ERA-2AED101X
RL1: 50; R_0402_1005Metric; MPN TNPW040249R9BEED
U1, U2, U3, U4, U5, U6, U7, U8, U9, U10, U11, U12: SKY13575-639LF; SW_SKY13575-639LF; MPN SKY13575-639LF
W1, W2, W3, W4, W5, W6: splitter; 50-70.7 Y; not fitted

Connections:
+3.3V: C140.1, C147.1, C148.1, C149.1, C151.1, C152.1, C153.1, C154.1, C155.1, C156.1, C158.1, C160.1, U1.10 (VDD), U2.10 (VDD), U3.10 (VDD), U4.10 (VDD), U5.10 (VDD), U6.10 (VDD), U7.10 (VDD), U8.10 (VDD), U9.10 (VDD), U10.10 (VDD), U11.10 (VDD), U12.10 (VDD); also elsewhere on the board
/STEM/FAN_A/IN: C161.2; also elsewhere on the board
/STEM/FAN_B/IN: C162.2; also elsewhere on the board
/STEM/FAN_C/IN: C163.2; also elsewhere on the board
/STEM/FAN_D/IN: C165.2; also elsewhere on the board
/STEM/FAN_E/IN: C166.2; also elsewhere on the board
/STEM/FAN_F/IN: C167.2; also elsewhere on the board
/STEM/IN: W1.1 (In); also elsewhere on the board
/STEM/n20_a: U1.14 (RF1), U7.5 (RF4)
/STEM/n20_b: U2.14 (RF1), U8.5 (RF4)
/STEM/n20_c: U3.14 (RF1), U9.5 (RF4)
/STEM/n20_d: U4.12 (RF2), U10.7 (RF3)
/STEM/n20_e: U5.12 (RF2), U11.7 (RF3)
/STEM/n20_f: U6.12 (RF2), U12.7 (RF3)
/STEM/n45_a: U1.5 (RF4), U7.14 (RF1)
/STEM/n45_b: U2.5 (RF4), U8.14 (RF1)
/STEM/n45_c: U3.5 (RF4), U9.14 (RF1)
/STEM/n45_d: U4.7 (RF3), U10.12 (RF2)
/STEM/n45_e: U5.7 (RF3), U11.12 (RF2)
/STEM/n45_f: U6.7 (RF3), U12.12 (RF2)
/STEM/p30_a: U1.7 (RF3), U7.12 (RF2)
/STEM/p30_b: U2.7 (RF3), U8.12 (RF2)
/STEM/p30_c: U3.7 (RF3), U9.12 (RF2)
/STEM/p30_d: U4.5 (RF4), U10.14 (RF1)
/STEM/p30_e: U5.5 (RF4), U11.14 (RF1)
/STEM/p30_f: U6.5 (RF4), U12.14 (RF1)
/STEM/zero_a: U1.12 (RF2), U7.7 (RF3)
/STEM/zero_b: U2.12 (RF2), U8.7 (RF3)
/STEM/zero_c: U3.12 (RF2), U9.7 (RF3)
/STEM/zero_d: U4.14 (RF1), U10.5 (RF4)
/STEM/zero_e: U5.14 (RF1), U11.5 (RF4)
/STEM/zero_f: U6.14 (RF1), U12.5 (RF4)
GND: C140.2, C147.2, C148.2, C149.2, C151.2, C152.2, C153.2, C154.2, C155.2, C156.2, C158.2, C160.2, RL1.2, U1.1 (GND), U1.3 (GND), U1.4 (GND), U1.6 (GND), U1.11 (GND), U1.13 (GND), U1.15 (EPAD), U2.1 (GND), U2.3 (GND), U2.4 (GND), U2.6 (GND), U2.11 (GND), U2.13 (GND), U2.15 (EPAD), U3.1 (GND), U3.3 (GND), U3.4 (GND), U3.6 (GND), U3.11 (GND), U3.13 (GND), U3.15 (EPAD), U4.1 (GND), U4.3 (GND), U4.4 (GND), U4.6 (GND), U4.11 (GND), U4.13 (GND), U4.15 (EPAD), U5.1 (GND), U5.3 (GND), U5.4 (GND), U5.6 (GND), U5.11 (GND), U5.13 (GND), U5.15 (EPAD), U6.1 (GND), U6.3 (GND), U6.4 (GND), U6.6 (GND), U6.11 (GND), U6.13 (GND), U6.15 (EPAD), U7.1 (GND), U7.3 (GND), U7.4 (GND), U7.6 (GND), U7.11 (GND), U7.13 (GND), U7.15 (EPAD), U8.1 (GND), U8.3 (GND), U8.4 (GND), U8.6 (GND), U8.11 (GND), U8.13 (GND), U8.15 (EPAD), U9.1 (GND), U9.3 (GND), U9.4 (GND), U9.6 (GND), U9.11 (GND), U9.13 (GND), U9.15 (EPAD), U10.1 (GND), U10.3 (GND), U10.4 (GND), U10.6 (GND), U10.11 (GND), U10.13 (GND), U10.15 (EPAD), U11.1 (GND), U11.3 (GND), U11.4 (GND), U11.6 (GND), U11.11 (GND), U11.13 (GND), U11.15 (EPAD), U12.1 (GND), U12.3 (GND), U12.4 (GND), U12.6 (GND), U12.11 (GND), U12.13 (GND), U12.15 (EPAD); also elsewhere on the board
unnamed: C168.2, U1.2 (RFC)
unnamed: C169.2, U2.2 (RFC)
unnamed: C170.2, U3.2 (RFC)
unnamed: C172.2, U4.2 (RFC)
unnamed: C174.2, U5.2 (RFC)
unnamed: C175.2, U6.2 (RFC)
unnamed: C161.1, U7.2 (RFC)
unnamed: C162.1, U8.2 (RFC)
unnamed: C163.1, U9.2 (RFC)
unnamed: C165.1, U10.2 (RFC)
unnamed: C166.1, U11.2 (RFC)
unnamed: C167.1, U12.2 (RFC)
unnamed: R1.1, W1.2 (Out1), W2.1 (In)
unnamed: R1.2, W1.3 (Out2), W3.1 (In)
unnamed: R2.1, W2.2 (Out1), W4.1 (In)
unnamed: R2.2, W2.3 (Out2), W5.1 (In)
unnamed: R3.1, W3.2 (Out1), W6.1 (In)
unnamed: R3.2, RL1.1, W3.3 (Out2)
unnamed: C168.1, R4.1, W4.2 (Out1)
unnamed: C169.1, R4.2, W4.3 (Out2)
unnamed: C170.1, R5.1, W5.2 (Out1)
unnamed: C172.1, R5.2, W5.3 (Out2)
unnamed: C174.1, R6.1, W6.2 (Out1)
unnamed: C175.1, R6.2, W6.3 (Out2)
PHASE_CTRL_1: U1.8 (VC1), U2.8 (VC1), U3.8 (VC1), U4.8 (VC1), U5.8 (VC1), U6.8 (VC1); also elsewhere on the board
PHASE_CTRL_2: U1.9 (VC2), U2.9 (VC2), U3.9 (VC2), U10.9 (VC2), U11.9 (VC2), U12.9 (VC2); also elsewhere on the board
~PHASE_CTRL_1: U7.8 (VC1), U8.8 (VC1), U9.8 (VC1), U10.8 (VC1), U11.8 (VC1), U12.8 (VC1); also elsewhere on the board
~PHASE_CTRL_2: U4.9 (VC2), U5.9 (VC2), U6.9 (VC2), U7.9 (VC2), U8.9 (VC2), U9.9 (VC2); also elsewhere on the board

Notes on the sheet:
RF Switches for phase control
Microstrip Wilkinson power dividers
